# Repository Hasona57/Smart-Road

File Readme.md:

# Smart Road Eye: AI-Powered Traffic Management System

## Project Overview

**Smart Road Eye** is a traffic management system as I see a challenge that faces my country which is the conjestion and the bad traffic distribution and the bad traffic light function as sometimes you find the other road is very emepty and the second road is full but they must wait untill the traffic light count down that what make me want to made this project where it use AI vision through Raspberry Pi with camera module to detect cars and count them and detect emergency if there is one also another system to reduce the fast car speeds was added which is the ACTibump and another system for citzen which is the push button and the servo and there is a lane for emergency which is closed and open only if there is an emergency.

## Systems
- Detection system using Raspberry Pi 4 8Ram and camera module V2, but why cheaper RP cannot be used, because real-time computer vision needs a fast CPU and more memory that boards like Pi Zero or Pi 3 cannot provide. These boards cannot handle high-resolution camera input, run a model, and perform database communication. The RP4 8GB version offers enough processing power and RAM to handle detection and run it smoothly, as it can make more frames without lag, giving high accuracy.
- The speed ACTibump where IRs measure speed, and if it exceeds the limit, it opens the ACTibump to reduce the car speed.
- The push button, which indicates to the system that there are people who want to pass, and an ultrasonic sensor was added to reduce accidents, meaning keeping children safe.
- The lighting system where the LDR detects if it is night or day, then if it is night, the ultrasonic detects if there are cars or not to light the bulbs when it is needed (there is a car at night)

## Components
- Raspberry Pi 4 Model B (8GB RAM) (camera computer vision processing board)
- Raspberry Pi Camera Module v2 (camera module)
- MicroSD Card 64GB Class 10 (card used for Raspberry Pi System boot and load)
- Raspberry Pi 5V 3A USB-C Power Supply (The RP electric Supply)
- ESP32-DevKitC-32D (ESP-32 Development Board) (The main controller board)
- Traffic Light Module (3-Color LED Module) (the traffic light indication on the road)
- 3 x Servo Motor SG90 (Emergency Gate, Speed Bump, and Pedestrian Gate or citizen lane gate)
- MQ135 Gas Sensor Module (to detect air pollution in real life)
- IR Sensor Module (Speed Detection Sensor 1 and 2)
- LDR Module (Light Dependent Resistor) (detecting day or night)
- HC-SR04 Ultrasonic Sensor (detecting if there are cars at night)
- Push Button (Pedestrian Crossing System)
- 5V Relay Module (switch to control turning on and off the LEDs)
- I2C LCD Display 16x2 (screen to display output of the system)
- Jumper Wires (Male-to-Male), Breadboard (830 Points), and Jumper Wires (Male-to-Female) to perform connections
- 5V 3A Power Supply (External) (to power the project with sufficient supply)
- Resistor 220Ω 1/4W (for Street LEDs)
- White LED 5mm (Street Lights)
- HDMI to mini HDMI Cable (for Raspberry Pi) (to be connected with the monitor)
- 3 in 1 USB C SD Card Reader USB C to SD/Micro SD/USB 3.0 Adapter TF Memory Card Reader Compatible with Type C Devices (to upload the RP system)

## Components images
<div style="display: flex; flex-wrap: wrap; gap: 10px;">

</div>

## Construction
- Starting to make the project, we used a cardboard and drew on it the road and focused on one side of the road, then we colored the drawing and the result as shown in the following images
<div style="display: flex; flex-wrap: wrap; gap: 10px;">
  
</div>
- Secondly, we printed a 3D part as the stand that will carry the traffic light and the camera module, as shown in the 3D folder and in the images following
<div style="display: flex; flex-wrap: wrap; gap: 10px;">

</div>
- Third, we start adding the component that we can afford to get and make the connection beneath the road, and add some cups to carry it up upon the floor, then test the wired component in each system on its own, then test two systems, then check if all the systems are working together.

## AI
- First of all, I used the YOLO model directly without any training or making a specific model for my project, and it was good with actual images from real life, but for toy cars in the prototype, it always says mostly toy car without differentiation between the emergency and normal cars.
- Second, I used Edge Impulse as I saw a video on YouTube, so I tried to train a model using it, and the good thing is that it extracted as a library, so it can work offline so low latency, but I found a very low accuracy as it used a weak model for training.
- Third and will be used as it will be the most accurate way with RP which is using YOLO to train a specific model for my data and upload it to work on the RP local host and connected to the camera real-time sending the data real-time to the firebase and it will give higher accuracy as the YOLO is a heavy and strong model that I tested by the ESP32 CAM and it was accurate but the latency it very high it may take 20 minutes to change sence so we changed our mind to using RP as the main AI detection unit as it use local server that is not on a laptop or another device so it use network no as the camera is connected direct so it work face with very low latency also because its high processing unit it give higher frames with higher accuracy with a very low latency.

## How it works
- The Raspberry Pi sends the result through a real-time Firebase database, then the ESP32 receives it and processes it to choose if action needs to be taken, whether to change the traffic light time or to open the emergency gate, and the ESP32 processes other systems (light, push button, and speed bump)
- The app gets data from the Firebase to display real-time data

## Changing the Raspberry Pi to match the budget
- PI zero 2 W, it is cheap, but its RAM and processor won't work for detection, so we searched a lot until we found RP 3B+, which is not good for detection either, but it is better than the zero 2 W and won't exceed the budget. and here is images for the least price we found
<div style="display: flex; flex-wrap: wrap; gap: 10px;">

</div>

## Full assembly images till now
<div style="display: flex; flex-wrap: wrap; gap: 10px;">

</div>

## coding
- Python for the AI model and the RP code
- C++ for the ESP32 CAM code
- Dart for Flutter app code

## Links
- https://drive.google.com/drive/folders/1oXieUDFhaSvpWXGAfWP8MMazlWLh3bht?usp=drive_link (Folder for full assembly and 3D video render)
- https://drive.google.com/drive/folders/1KsriBLeugqPdMsl5KT9PRbp6rbyMKrla?usp=sharing (3D Blender file)
- https://wokwi.com/projects/453308781447889921 (Arduino code)
- https://wokwi.com/projects/453387951416239105 (ESP32 code)

## cost
- As shown in [BOM.csv](https://github.com/Hasona57/Smart-Road/blob/79e5c046aa0be40c0b9f62295015dc0e1bf572b4/BOM.csv) approxmate price is 8835 EGP
- For me, I have some of the components as I have an LCD I2C, a Push button, an LDR, 3 servos, a traffic light, a breadboard, an ESP32, LEDs, a Relay, a 5V Adapter, some Resistance, and 2 IRs, so it will be ~7935.5 EGP (Egyptian Pounds)

## This project is for Hack Club Blueprint for more information [Hack-Club-Blueprint](https://blueprint.hackclub.com/)

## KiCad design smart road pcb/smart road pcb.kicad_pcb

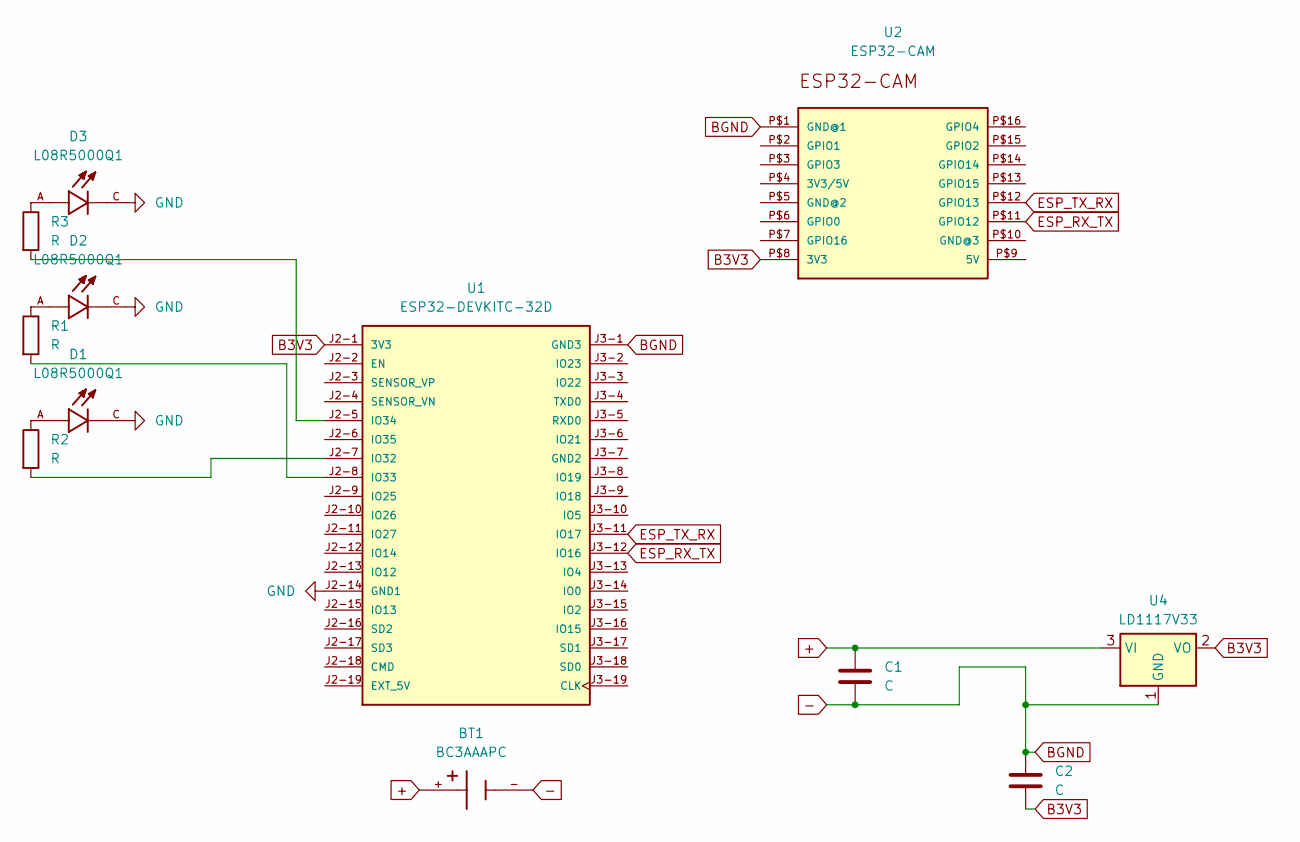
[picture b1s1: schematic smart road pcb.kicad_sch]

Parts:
BT1: BC3AAAPC; BAT_BC3AAAPC; PARTREV F
C1: C; C_Disc_D5.0mm_W2.5mm_P5.00mm
C2: C; CP_Radial_D5.0mm_P2.50mm
D1, D2, D3: L08R5000Q1; LEDRD254W57D500H1070; PARTREV NA
R1, R2, R3: R; R_0201_0603Metric_Pad0.64x0.40mm_HandSolder
U1: ESP32-DEVKITC-32D; MODULE_ESP32-DEVKITC-32D; PARTREV V4
U2: ESP32-CAM
U4: LD1117V33; TO-220-3_Vertical

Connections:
+: BT1.+, C1.1, U4.3 (VI)
-: BT1.-, C1.2, C2.1, U1.J3-1 (GND3), U2.P$1 (GND@1), U4.1 (GND)
B3V3: C2.2, U1.J2-1 (3V3), U2.P$8 (3V3), U4.2 (VO)
ESP_RX_TX: U1.J3-12 (IO16), U2.P$11 (GPIO12)
ESP_TX_RX: U1.J3-11 (IO17), U2.P$12 (GPIO13)
GND: D1.C, D2.C, D3.C, U1.J2-14 (GND1)
unnamed: D1.A, R2.1
unnamed: D2.A, R1.1
unnamed: D3.A, R3.1
unnamed: R2.2, U1.J2-7 (IO32)
unnamed: R1.2, U1.J2-8 (IO33)
unnamed: R3.2, U1.J2-5 (IO34)

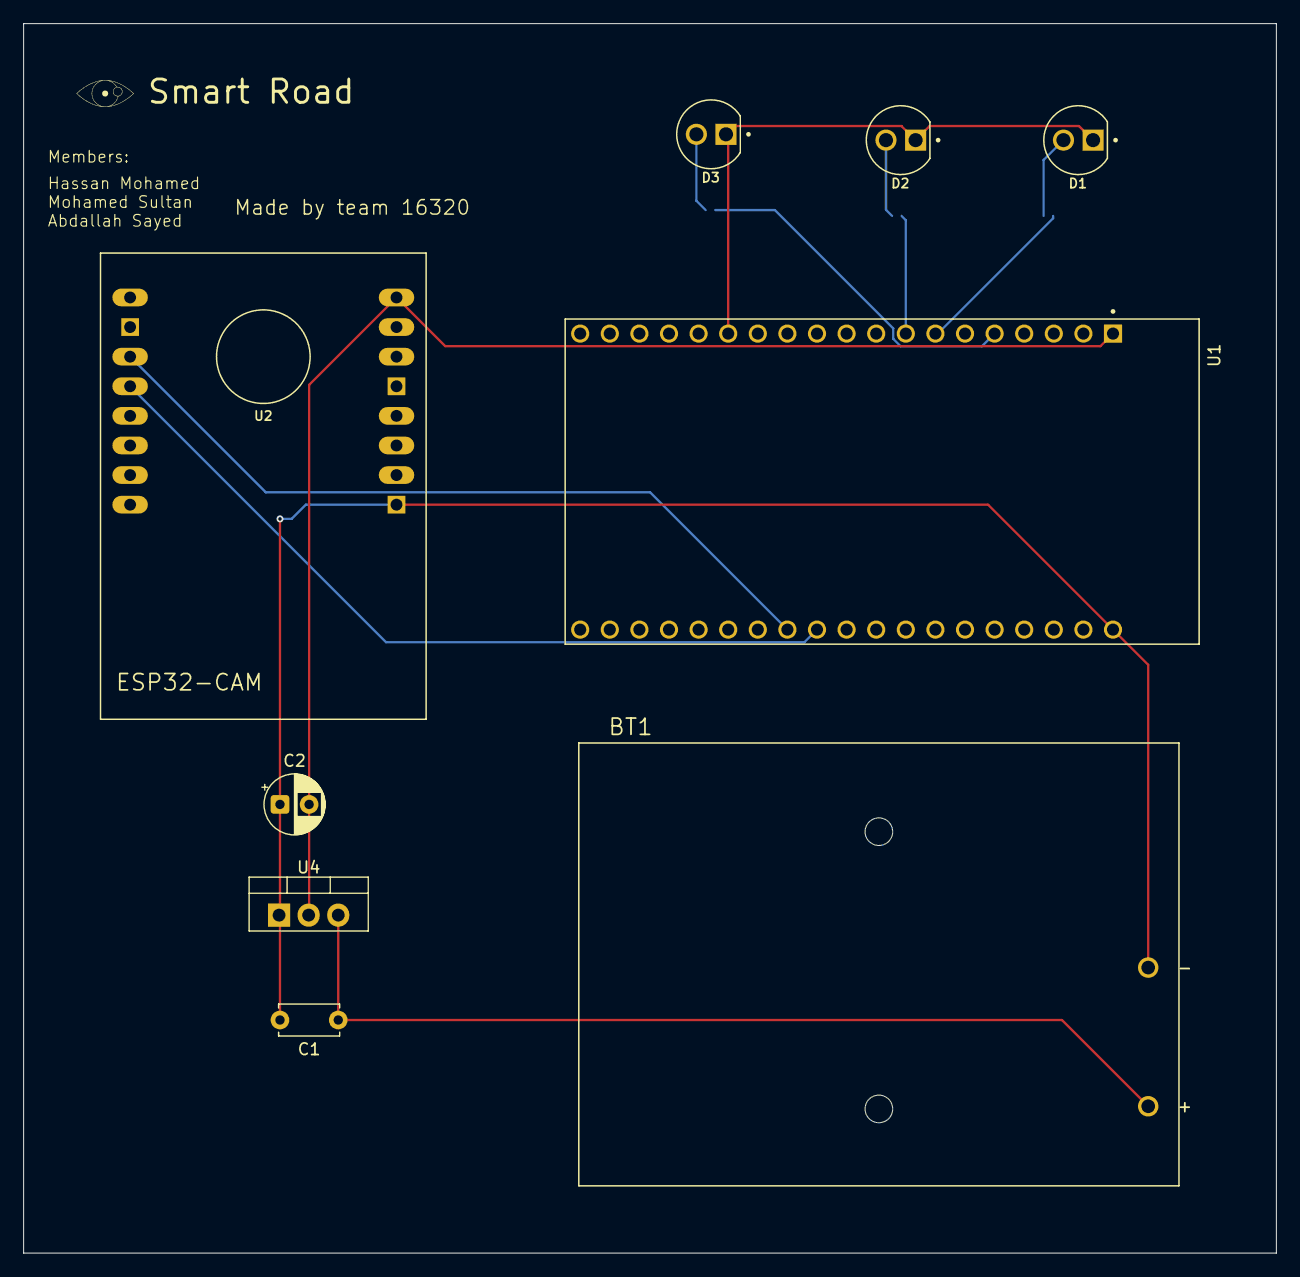
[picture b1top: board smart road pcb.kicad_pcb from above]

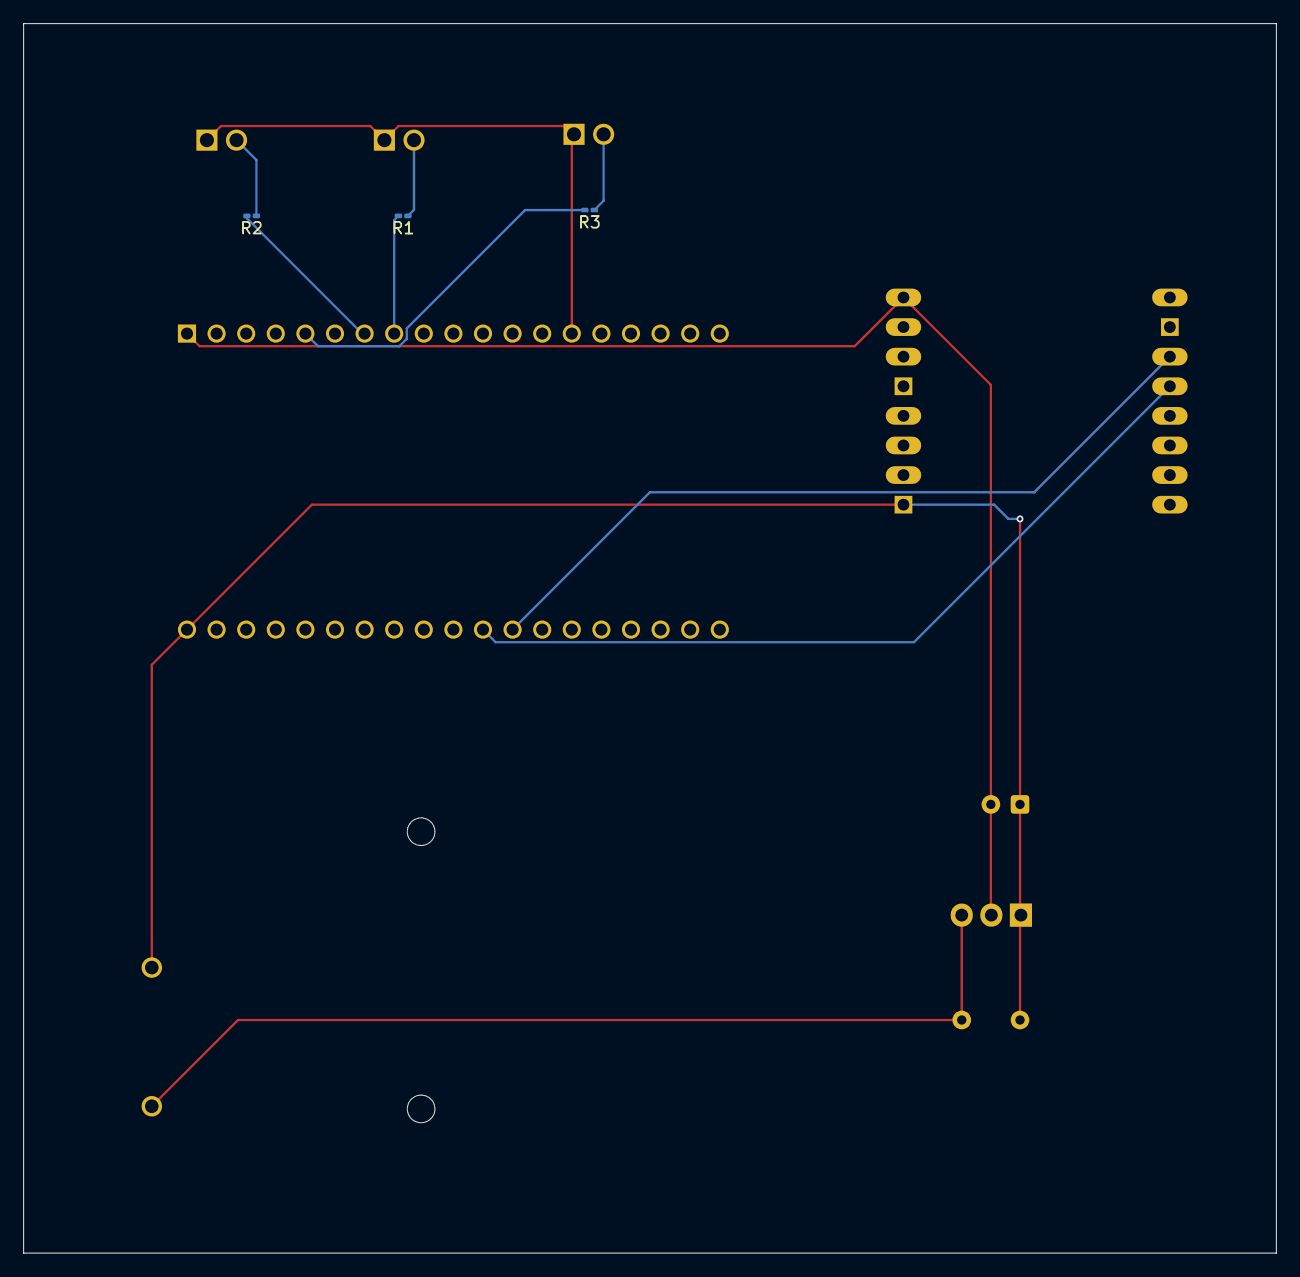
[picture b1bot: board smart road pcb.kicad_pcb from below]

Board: 2 copper layers, 107.5 x 105.5 mm, 12 parts (3 on the bottom side), 12 nets.

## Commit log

2025-11-14 edit PCB and making case
2025-11-14 Readme.md
2025-11-14 after closing
2025-11-15 adding images
2025-11-18 Adding BOM
2025-12-07 a lot of changes
2025-12-07 Raspberry Pi
2025-12-07 fix readme.md
2025-12-09 code edit
2025-12-10 Change image reference to direct GitHub link
    Updated image reference in Readme.md to a direct link.
2025-12-10 Rename Screenshot 2025-12-10 055634.png to 3D1
2025-12-10 Rename Screenshot 2025-12-10 055656.png to 3D2
2025-12-10 Rename Screenshot 2025-12-10 055706.png to 3D3
2025-12-10 Rename 3D3 to 3D3.png
2025-12-10 Rename 3D1 to 3D1.png
2025-12-10 Rename 3D2 to 3D2.png
2025-12-10 Rename push button.jpg to pushbutton.jpg
2025-12-10 Rename Raspeberry Pi Camera V2.jpg to RaspeberryPiCameraV2.jpg
2025-12-10 Rename HDMI to Micro HDMI.jpg to HDMItoMicroHDMI.jpg
2025-12-10 Rename Raspberry Pi Type C adapter.jpg to RaspberryPiTypeCadapter.jpg
2025-12-10 Rename Resistor 220 ohm 0.25W.jpg to Resistor220ohm0.25W.jpg
2025-12-10 Rename SD card.jpg to SDcard.jpg
2025-12-10 Rename Type C to SD card.jpg to TypeCtoSDcard.jpg
2025-12-10 Rename traffic light module.jpg to trafficlightmodule.jpg
2025-12-10 Fix wording in BOM and update total cost
    Corrected wording and updated approximate total cost.
2025-12-10 Update Readme with project details and structure
    Revised project overview, systems, components, and construction details for clarity and organization.
